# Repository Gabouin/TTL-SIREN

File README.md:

# TTL BASED POLICE SIREN

## [FALSTAD](https://is.gd/G7ro6Q) SIMULATION 

#### The two transistors alternately switch on and off because when one transistor turns on, it prevents the other from conducting by pulling its base voltage low. The capacitors charge and discharge through the resistors, creating a timing delay that makes the transistors switch states repeatedly, causing the LEDs to blink back and forth, like a siren.
#### My final TTL circuit is basicaly an astable multivibrator that is meant to look like a **police siren** !
#### I choose to make that because I was stuck looking for an idea and ended up having this popping in my head and I tought it would be fun to add in a 3D printed translucent enclosure to make maybe a real-looking police siren for cosplay.
<br>  

## SCHEM DESIGN

I made the schematic on KiCad :

## PCB DESIGN 

### Components placement

I made an edge cut's shape based on a police siren and put all the components inside to have the blue LEDS on one side and the red LEDS on the other side, the other components in the middle with still somewhere to add silkscreen.  

<div align=center>
  
</div>

### Silkscreen

<div align="center">
  <table>
    <tr>
      <td valign="bottom"></td>
      <td valign="bottom">
</td>
      <td valign="bottom"></td>
      <td valign="bottom"> </td>

  </table>
</div>

<br>  

## BOM

|Designator                             |Footprint                                       |Quantity|Value     |LCSC Part #|
|---------------------------------------|------------------------------------------------|--------|----------|-----------|
|C1, C2                                 |C_Disc_D5.0mm_W2.5mm_P5.00mm                    |2       |12u       |           |
|D1, D10, D2, D3, D4, D5, D6, D7, D8, D9|LED_D5.0mm                                      |10      |LED       |           |
|J1                                     |PinHeader_1x02_P2.54mm_Vertical                 |1       |Conn_01x02|           |
|Q1, Q2                                 |TO-92L_Inline_Wide                              |2       |NPN       |           |
|R1, R4                                 |R_Axial_DIN0204_L3.6mm_D1.6mm_P7.62mm_Horizontal|2       |330       |           |
|R2, R3                                 |R_Axial_DIN0204_L3.6mm_D1.6mm_P7.62mm_Horizontal|2       |1k        |           |

_____________________________________________________________________________________________________________________________________________

#### This project was made for the 2nd week of RESOLUTION - Hack Club

Please take in conscious that lapse (and so hackatime) was only used for the falstad simulation (1 hou) but for the other steps I forgot to use it so the time wasn't counted and the Schem and PCB took me aprox 3hours

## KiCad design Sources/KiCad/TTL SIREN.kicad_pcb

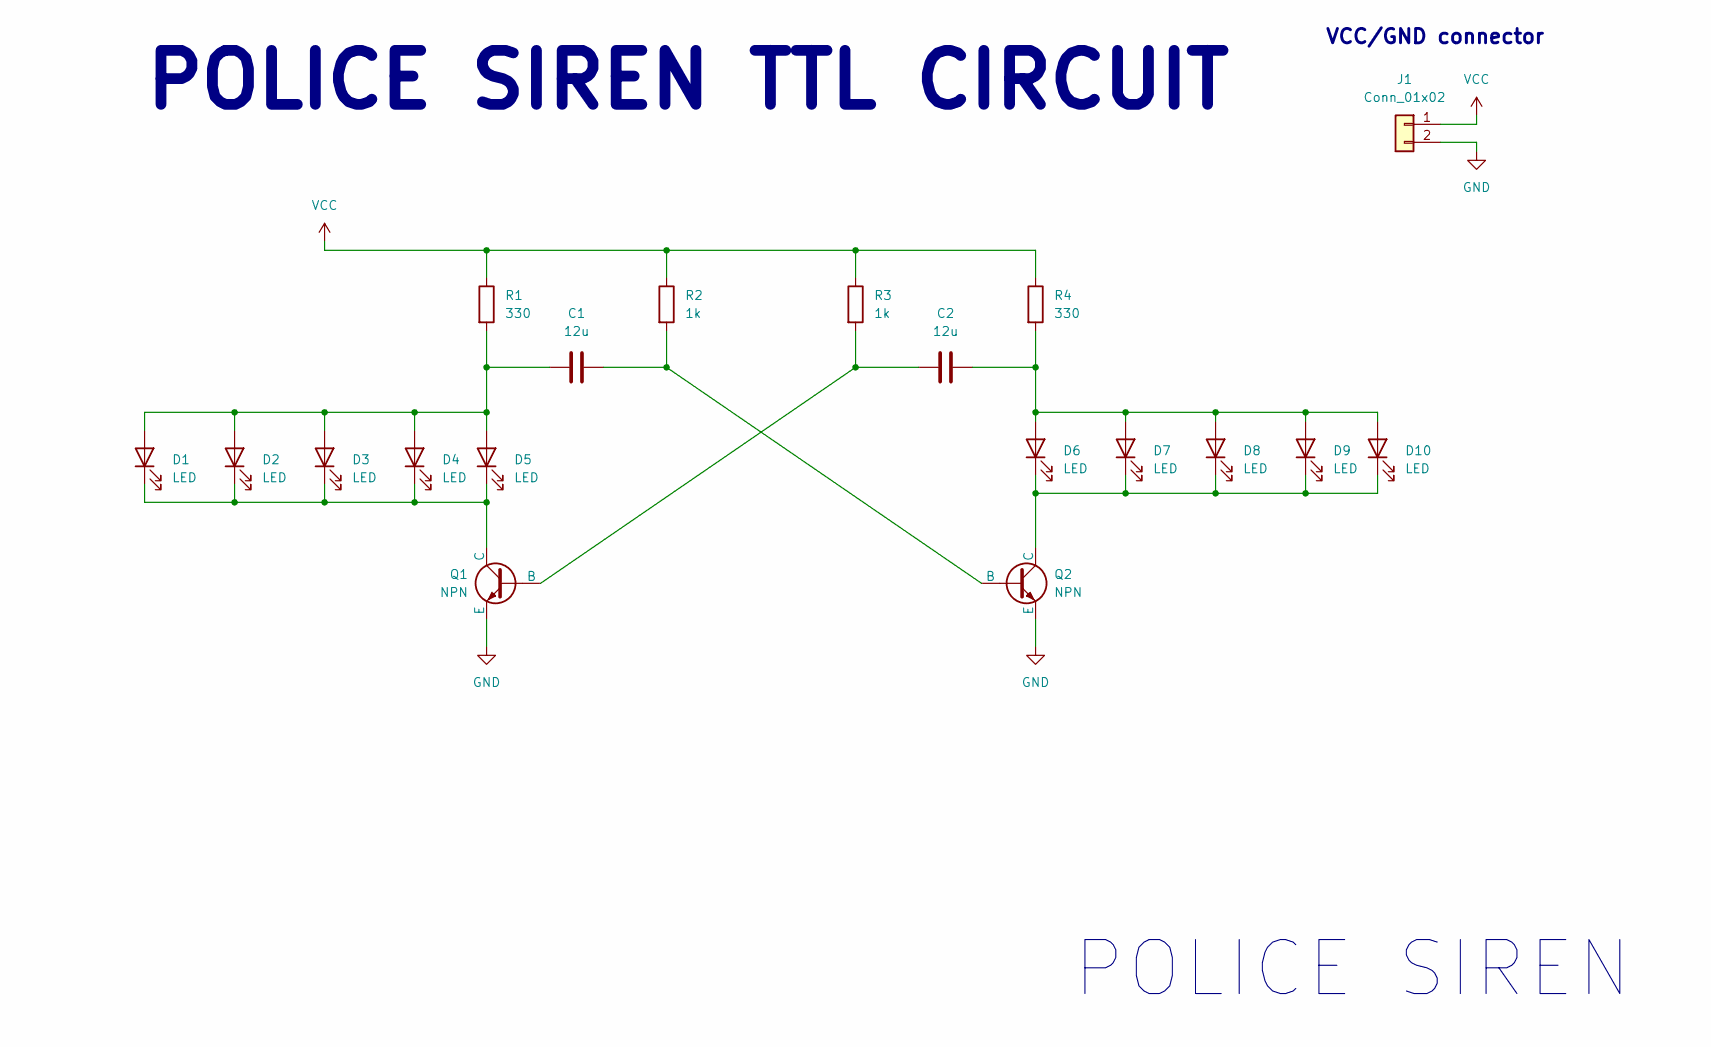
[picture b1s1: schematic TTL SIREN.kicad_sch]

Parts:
C1, C2: 12u; C_Disc_D5.0mm_W2.5mm_P5.00mm
D1, D2, D3, D4, D5, D6, D7, D8, D9, D10: LED; LED_D5.0mm
J1: Conn_01x02; PinHeader_1x02_P2.54mm_Vertical
Q1, Q2: NPN; TO-92L_Inline_Wide
R1, R4: 330; R_Axial_DIN0204_L3.6mm_D1.6mm_P7.62mm_Horizontal
R2, R3: 1k; R_Axial_DIN0204_L3.6mm_D1.6mm_P7.62mm_Horizontal

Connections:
GND: J1.2, Q1.3 (E), Q2.3 (E)
unnamed: C1.1, D1.2 (A), D2.2 (A), D3.2 (A), D4.2 (A), D5.2 (A), R1.2
unnamed: D1.1 (K), D2.1 (K), D3.1 (K), D4.1 (K), D5.1 (K), Q1.1 (C)
unnamed: C2.2, D6.2 (A), D7.2 (A), D8.2 (A), D9.2 (A), D10.2 (A), R4.2
unnamed: D6.1 (K), D7.1 (K), D8.1 (K), D9.1 (K), D10.1 (K), Q2.1 (C)
unnamed: C2.1, Q1.2 (B), R3.2
unnamed: C1.2, Q2.2 (B), R2.2
VCC: J1.1, R1.1, R2.1, R3.1, R4.1

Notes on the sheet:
POLICE SIREN TTL CIRCUIT
POLICE SIREN
VCC/GND connector

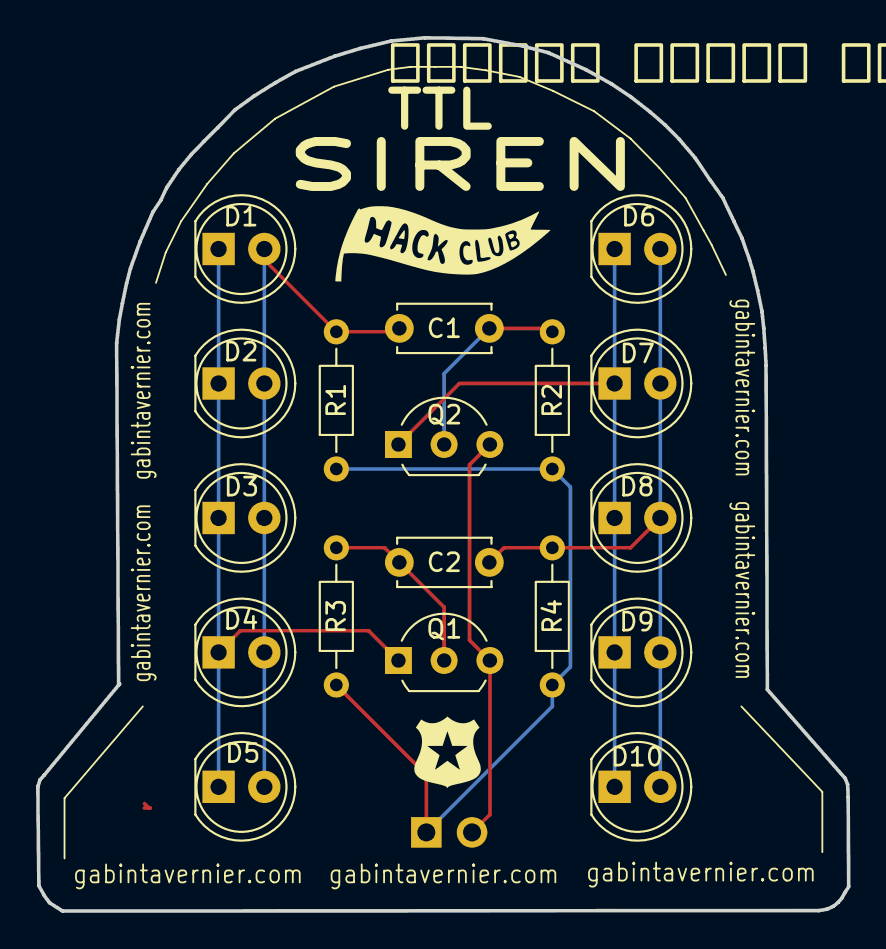
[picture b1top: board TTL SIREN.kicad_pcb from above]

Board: 2 copper layers, 45.1 x 48.5 mm, 19 parts (1 on the bottom side), 8 nets.

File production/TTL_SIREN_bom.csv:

Designator,Footprint,Quantity,Value,LCSC Part #
"C1, C2",C_Disc_D5.0mm_W2.5mm_P5.00mm,2,12u,
"D1, D10, D2, D3, D4, D5, D6, D7, D8, D9",LED_D5.0mm,10,LED,
J1,PinHeader_1x02_P2.54mm_Vertical,1,Conn_01x02,
"Q1, Q2",TO-92L_Inline_Wide,2,NPN,
"R1, R4",R_Axial_DIN0204_L3.6mm_D1.6mm_P7.62mm_Horizontal,2,330,
"R2, R3",R_Axial_DIN0204_L3.6mm_D1.6mm_P7.62mm_Horizontal,2,1k,

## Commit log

2026-04-08 Update README with astable multivibrator improvements
    Added details about the improved version of the astable multivibrator and included links to previous attempts and images.
2026-04-08 Rename netlist.ipc to production/netlist.ipc
2026-04-08 Rename FALSTAD/Police siren astable multivibrator.txt to Sources/FALSTAD/Police siren astable multivibrator.txt
2026-04-08 Rename Capture d'écran 2026-04-08 192825.png to images/whole PCB
2026-04-08 Rename images/Capture d'écran 2026-04-08 183714.png to officer griffin
2026-04-08 Rename Capture d'écran 2026-04-08 185930.png to whole pcb front
2026-04-08 Rename Capture d'écran 2026-04-08 192842.png to whole PCB routing
2026-04-22 Add BOM section to README
    Added Bill of Materials (BOM) section to README.

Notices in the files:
README.md:
License: MIT
